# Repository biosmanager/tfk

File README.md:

# tfk - The F(ine|fancy|inal) Keyboard

This is a work in progress collection of open-source high-end keyboard PCBs. 
Designed to be hand-solderable.

**Features**:

-   Compatible with QMK firmware and VIA
-   Hot-swap sockets
-   Per-key RGB lighting and RGB backlight
-   USB-C
-   Overvoltage, overcurrent and ESD protection
-   Hand-solderable footprints
-   (All powered by STM32 microcontrollers)

> **NOTE:**  Due to the current global chip crisis I decided to use AVR based microcontrollers in the first revisions which are easier to obtain.

## Keyboards

|Status | Name  | Size | # of keys | Description | MCU | Compatible cases (intended) |
|-------| ----- | ---- | --------- | ------------|-----|------------------|
| <span style="color: green">Active</span> | tfk21-avr | 20% | 21 | Numpad with extra row   | ATmega32U4 | [KPRepublic Cospad cases](https://kprepublic.com/collections/cospad-xd24) |
| <span style="color: red">On hold</span>  | tfk21     | 20% | 21 | Numpad with extra row   | STM32F072  | [KPRepublic Cospad cases](https://kprepublic.com/collections/cospad-xd24) |
| <span style="color: red">On hold</span>  | tfk84     | 75% | 84 | More compact than a TKL | STM32F303  | [KPRepublic XD84 cases](https://kprepublic.com/collections/xd84) |

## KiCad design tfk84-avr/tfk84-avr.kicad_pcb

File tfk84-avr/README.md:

# tfk84-avr

84 key hot-swap RGB 75% TKL keyboard. Uses Microchip ATmega32U4-AU microcontroller. 
All footprints should be suitable for hand soldering.

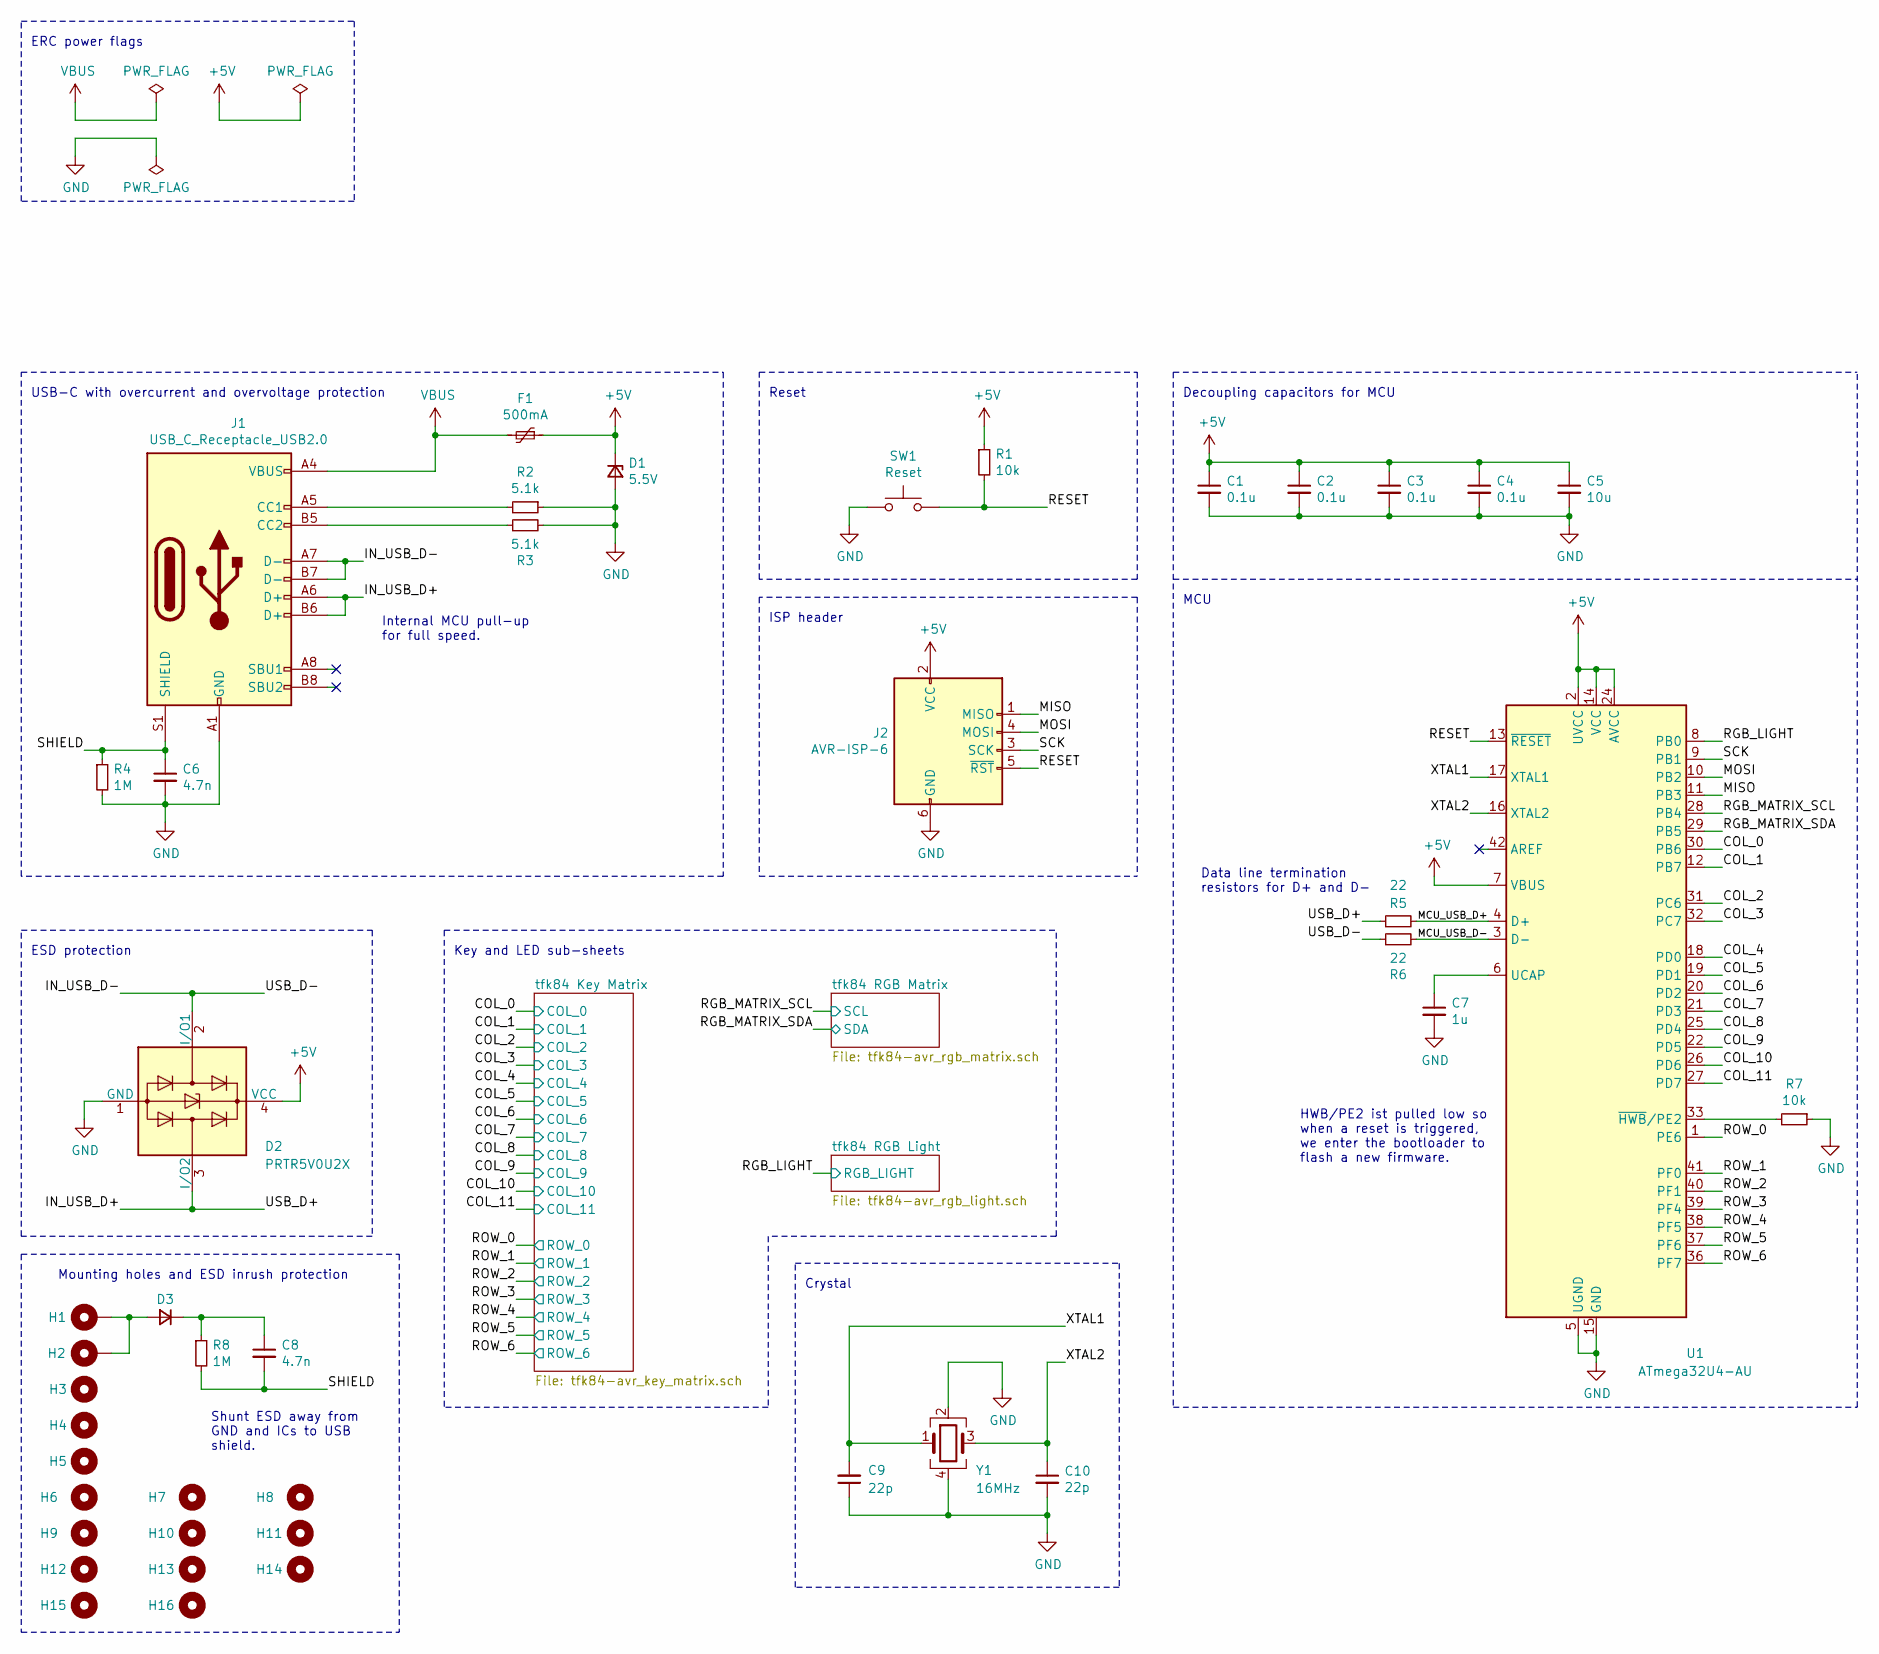
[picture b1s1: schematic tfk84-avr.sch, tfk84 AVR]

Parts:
C1, C2, C3, C4: 0.1u; C_0805_2012Metric_Pad1.18x1.45mm_HandSolder
C5: 10u; C_0805_2012Metric_Pad1.18x1.45mm_HandSolder
C6, C8: 4.7n; C_0805_2012Metric_Pad1.18x1.45mm_HandSolder
C7: 1u; C_0805_2012Metric_Pad1.18x1.45mm_HandSolder
C9, C10: 22p; C_0805_2012Metric_Pad1.18x1.45mm_HandSolder
D1: 5.5V; D_SOD-123
D2: PRTR5V0U2X; SOT-143
D3: Case ESD; D_SOD-123
F1: 500mA; Fuse_1206_3216Metric_Pad1.42x1.75mm_HandSolder
H1, H2: Case; MountingHole_2.5mm_Pad
H3, H4, H5, H6, H7, H8, H9, H10, H11, H12, H13, H14, H15, H16: MountingHole; MountingHole_4.5x2.5mm_Pad_TopOnly_NPTH
J1: USB_C_Receptacle_USB2.0; USB_C_Receptacle_HRO_TYPE-C-31-M-12
J2: AVR-ISP-6; Reset_Pretty-Mask
R1, R7: 10k; R_0805_2012Metric_Pad1.20x1.40mm_HandSolder
R2, R3: 5.1k; R_0805_2012Metric_Pad1.20x1.40mm_HandSolder
R4, R8: 1M; R_0805_2012Metric_Pad1.20x1.40mm_HandSolder
R5, R6: 22; R_0805_2012Metric_Pad1.20x1.40mm_HandSolder
SW1: Reset; SKQG-1155865
U1: ATmega32U4-AU; TQFP-44_10x10mm_P0.8mm
Y1: 16MHz; Crystal_SMD_3225-4Pin_3.2x2.5mm_HandSoldering

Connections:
+5V: C1.1, C2.1, C3.1, C4.1, C5.1, D1.1 (K), D2.4 (VCC), F1.1, J2.2 (VCC), R1.1, U1.2 (UVCC), U1.7 (VBUS), U1.14 (VCC), U1.24 (AVCC), U1.34 (VCC), U1.44 (AVCC); also elsewhere on the board
/COL_0: U1.30 (PB6); also elsewhere on the board
/COL_1: U1.12 (PB7); also elsewhere on the board
/COL_2: U1.31 (PC6); also elsewhere on the board
/COL_3: U1.32 (PC7); also elsewhere on the board
/COL_4: U1.18 (PD0); also elsewhere on the board
/COL_5: U1.19 (PD1); also elsewhere on the board
/COL_6: U1.20 (PD2); also elsewhere on the board
/COL_7: U1.21 (PD3); also elsewhere on the board
/COL_8: U1.25 (PD4); also elsewhere on the board
/COL_9: U1.22 (PD5); also elsewhere on the board
/COL_10: U1.26 (PD6); also elsewhere on the board
/COL_11: U1.27 (PD7); also elsewhere on the board
/IN_USB_D+: D2.3 (I/O2), J1.A6 (D+), J1.B6 (D+), R5.1
/IN_USB_D-: D2.2 (I/O1), J1.A7 (D-), J1.B7 (D-), R6.1
/MCU_USB_D+: R5.2, U1.4 (D+)
/MCU_USB_D-: R6.2, U1.3 (D-)
/MISO: J2.1 (MISO), U1.11 (PB3)
/MOSI: J2.4 (MOSI), U1.10 (PB2)
/RESET: J2.5 (~RST), R1.2, SW1.2, U1.13 (~RESET)
/RGB_LIGHT: U1.8 (PB0); also elsewhere on the board
/RGB_MATRIX_SCL: U1.28 (PB4); also elsewhere on the board
/RGB_MATRIX_SDA: U1.29 (PB5); also elsewhere on the board
/ROW_0: U1.1 (PE6); also elsewhere on the board
/ROW_1: U1.41 (PF0); also elsewhere on the board
/ROW_2: U1.40 (PF1); also elsewhere on the board
/ROW_3: U1.39 (PF4); also elsewhere on the board
/ROW_4: U1.38 (PF5); also elsewhere on the board
/ROW_5: U1.37 (PF6); also elsewhere on the board
/ROW_6: U1.36 (PF7); also elsewhere on the board
/SCK: J2.3 (SCK), U1.9 (PB1)
/SHIELD: C6.1, C8.2, J1.S1 (SHIELD), R4.1, R8.2
/XTAL1: C9.2, U1.17 (XTAL1), Y1.1
/XTAL2: C10.1, U1.16 (XTAL2), Y1.3
GND: C1.2, C2.2, C3.2, C4.2, C5.2, C6.2, C7.2, C9.1, C10.2, D1.2 (A), D2.1 (GND), J1.A1 (GND), J1.A12 (GND), J1.B1 (GND), J1.B12 (GND), J2.6 (GND), R2.1, R3.2, R4.2, R7.1, SW1.1, U1.5 (UGND), U1.15 (GND), U1.23 (GND), U1.35 (GND), U1.43 (GND), Y1.2, Y1.4; also elsewhere on the board
unnamed: C7.1, U1.6 (UCAP)
unnamed: C8.1, D3.1 (K), R8.1
unnamed: D3.2 (A), H1.1, H2.1
unnamed: J1.A5 (CC1), R2.2
unnamed: J1.B5 (CC2), R3.1
unnamed: R7.2, U1.33 (~HWB~/PE2)
VBUS: F1.2, J1.A4 (VBUS), J1.A9 (VBUS), J1.B4 (VBUS), J1.B9 (VBUS)

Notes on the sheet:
Internal MCU pull-up for full speed.
Decoupling capacitors for MCU
USB-C with overcurrent and overvoltage protection
Key and LED sub-sheets
ERC power flags
Mounting holes and ESD inrush protection
Shunt ESD away from GND and ICs to USB shield.
Data line termination resistors for D+ and D-
ESD protection
MCU
Crystal
HWB/PE2 ist pulled low so when a reset is triggered, we enter the bootloader to flash a new firmware.
Reset
ISP header

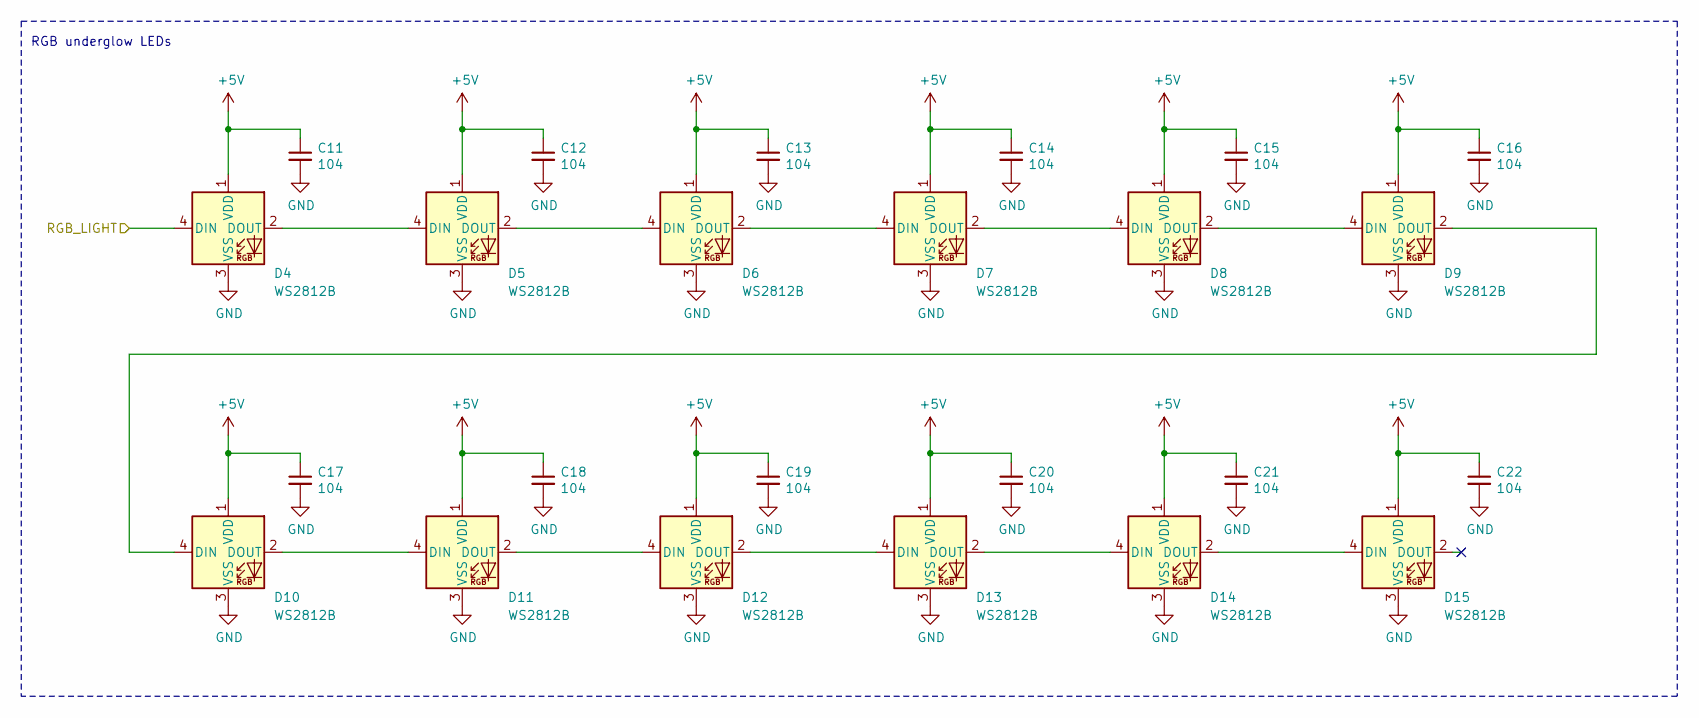
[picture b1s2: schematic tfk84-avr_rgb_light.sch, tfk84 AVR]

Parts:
C11, C12, C13, C14, C15, C16, C17, C18, C19, C20, C21, C22: 104; C_0805_2012Metric_Pad1.18x1.45mm_HandSolder
D4, D5, D6, D7, D8, D9, D10, D11, D12, D13, D14, D15: WS2812B; LED_WS2812B_PLCC4_5.0x5.0mm_P3.2mm

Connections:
+5V: C11.1, C12.1, C13.1, C14.1, C15.1, C16.1, C17.1, C18.1, C19.1, C20.1, C21.1, C22.1, D4.1 (VDD), D5.1 (VDD), D6.1 (VDD), D7.1 (VDD), D8.1 (VDD), D9.1 (VDD), D10.1 (VDD), D11.1 (VDD), D12.1 (VDD), D13.1 (VDD), D14.1 (VDD), D15.1 (VDD); also elsewhere on the board
/RGB_LIGHT: D4.4 (DIN); also elsewhere on the board
GND: C11.2, C12.2, C13.2, C14.2, C15.2, C16.2, C17.2, C18.2, C19.2, C20.2, C21.2, C22.2, D4.3 (VSS), D5.3 (VSS), D6.3 (VSS), D7.3 (VSS), D8.3 (VSS), D9.3 (VSS), D10.3 (VSS), D11.3 (VSS), D12.3 (VSS), D13.3 (VSS), D14.3 (VSS), D15.3 (VSS); also elsewhere on the board
unnamed: D4.2 (DOUT), D5.4 (DIN)
unnamed: D5.2 (DOUT), D6.4 (DIN)
unnamed: D6.2 (DOUT), D7.4 (DIN)
unnamed: D7.2 (DOUT), D8.4 (DIN)
unnamed: D8.2 (DOUT), D9.4 (DIN)
unnamed: D10.2 (DOUT), D11.4 (DIN)
unnamed: D9.2 (DOUT), D10.4 (DIN)
unnamed: D11.2 (DOUT), D12.4 (DIN)
unnamed: D12.2 (DOUT), D13.4 (DIN)
unnamed: D13.2 (DOUT), D14.4 (DIN)
unnamed: D14.2 (DOUT), D15.4 (DIN)

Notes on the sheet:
RGB underglow LEDs

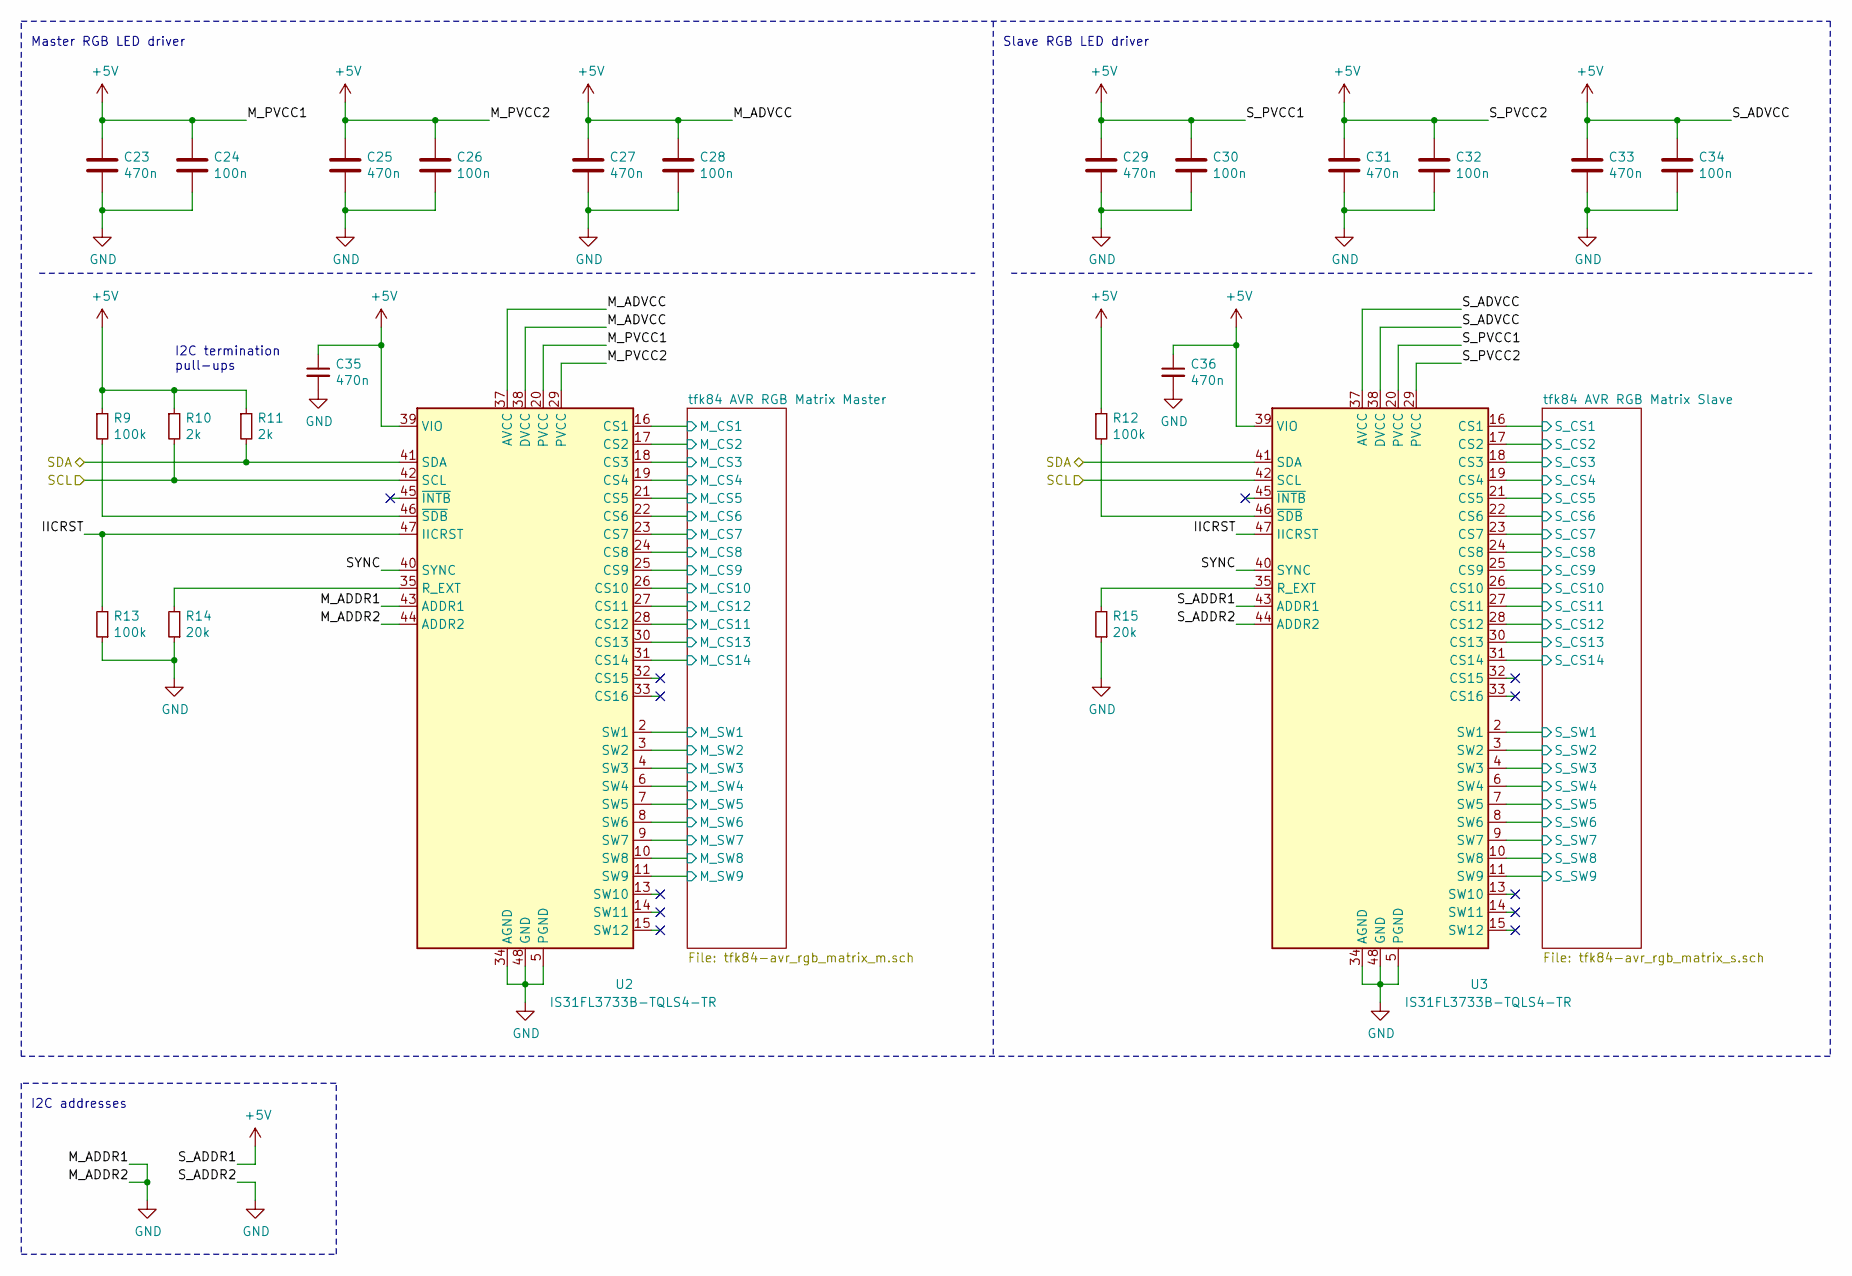
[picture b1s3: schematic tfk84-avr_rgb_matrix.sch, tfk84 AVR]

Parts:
C23, C25, C27, C29, C31, C33, C35, C36: 470n; C_0805_2012Metric_Pad1.18x1.45mm_HandSolder
C24, C26, C28, C30, C32, C34: 100n; C_0805_2012Metric_Pad1.18x1.45mm_HandSolder
R9, R12, R13: 100k; R_0805_2012Metric_Pad1.20x1.40mm_HandSolder
R10, R11: 2k; R_0805_2012Metric_Pad1.20x1.40mm_HandSolder
R14, R15: 20k; R_0805_2012Metric_Pad1.20x1.40mm_HandSolder
U2, U3: IS31FL3733B-TQLS4-TR; TQFP-48-1EP_7x7mm_P0.5mm_EP5x5mm_ThermalVias

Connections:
+5V: C23.1, C24.1, C25.1, C26.1, C27.1, C28.2, C29.1, C30.1, C31.1, C32.1, C33.1, C34.2, C35.1, C36.1, R9.1, R10.1, R11.1, R12.1, U2.20 (PVCC), U2.29 (PVCC), U2.37 (AVCC), U2.38 (DVCC), U2.39 (VIO), U3.20 (PVCC), U3.29 (PVCC), U3.37 (AVCC), U3.38 (DVCC), U3.39 (VIO), U3.43 (ADDR1); also elsewhere on the board
/RGB_MATRIX_SCL: R10.2, U2.42 (SCL), U3.42 (SCL); also elsewhere on the board
/RGB_MATRIX_SDA: R11.2, U2.41 (SDA), U3.41 (SDA); also elsewhere on the board
/tfk84 RGB Matrix/IICRST: R13.2, U2.47 (IICRST), U3.47 (IICRST)
/tfk84 RGB Matrix/SYNC: U2.40 (SYNC), U3.40 (SYNC)
/tfk84 RGB Matrix/tfk84 AVR RGB Matrix Master/M_CS1: U2.16 (CS1); also elsewhere on the board
/tfk84 RGB Matrix/tfk84 AVR RGB Matrix Master/M_CS2: U2.17 (CS2); also elsewhere on the board
/tfk84 RGB Matrix/tfk84 AVR RGB Matrix Master/M_CS3: U2.18 (CS3); also elsewhere on the board
/tfk84 RGB Matrix/tfk84 AVR RGB Matrix Master/M_CS4: U2.19 (CS4); also elsewhere on the board
/tfk84 RGB Matrix/tfk84 AVR RGB Matrix Master/M_CS5: U2.21 (CS5); also elsewhere on the board
/tfk84 RGB Matrix/tfk84 AVR RGB Matrix Master/M_CS6: U2.22 (CS6); also elsewhere on the board
/tfk84 RGB Matrix/tfk84 AVR RGB Matrix Master/M_CS7: U2.23 (CS7); also elsewhere on the board
/tfk84 RGB Matrix/tfk84 AVR RGB Matrix Master/M_CS8: U2.24 (CS8); also elsewhere on the board
/tfk84 RGB Matrix/tfk84 AVR RGB Matrix Master/M_CS9: U2.25 (CS9); also elsewhere on the board
/tfk84 RGB Matrix/tfk84 AVR RGB Matrix Master/M_CS10: U2.26 (CS10); also elsewhere on the board
/tfk84 RGB Matrix/tfk84 AVR RGB Matrix Master/M_CS11: U2.28 (CS12); also elsewhere on the board
/tfk84 RGB Matrix/tfk84 AVR RGB Matrix Master/M_CS12: U2.27 (CS11); also elsewhere on the board
/tfk84 RGB Matrix/tfk84 AVR RGB Matrix Master/M_CS13: U2.30 (CS13); also elsewhere on the board
/tfk84 RGB Matrix/tfk84 AVR RGB Matrix Master/M_CS14: U2.31 (CS14); also elsewhere on the board
/tfk84 RGB Matrix/tfk84 AVR RGB Matrix Master/M_SW1: U2.2 (SW1); also elsewhere on the board
/tfk84 RGB Matrix/tfk84 AVR RGB Matrix Master/M_SW2: U2.3 (SW2); also elsewhere on the board
/tfk84 RGB Matrix/tfk84 AVR RGB Matrix Master/M_SW3: U2.4 (SW3); also elsewhere on the board
/tfk84 RGB Matrix/tfk84 AVR RGB Matrix Master/M_SW4: U2.6 (SW4); also elsewhere on the board
/tfk84 RGB Matrix/tfk84 AVR RGB Matrix Master/M_SW5: U2.7 (SW5); also elsewhere on the board
/tfk84 RGB Matrix/tfk84 AVR RGB Matrix Master/M_SW6: U2.8 (SW6); also elsewhere on the board
/tfk84 RGB Matrix/tfk84 AVR RGB Matrix Master/M_SW7: U2.9 (SW7); also elsewhere on the board
/tfk84 RGB Matrix/tfk84 AVR RGB Matrix Master/M_SW8: U2.10 (SW8); also elsewhere on the board
/tfk84 RGB Matrix/tfk84 AVR RGB Matrix Master/M_SW9: U2.11 (SW9); also elsewhere on the board
/tfk84 RGB Matrix/tfk84 AVR RGB Matrix Slave/S_CS1: U3.16 (CS1); also elsewhere on the board
/tfk84 RGB Matrix/tfk84 AVR RGB Matrix Slave/S_CS2: U3.17 (CS2); also elsewhere on the board
/tfk84 RGB Matrix/tfk84 AVR RGB Matrix Slave/S_CS3: U3.18 (CS3); also elsewhere on the board
/tfk84 RGB Matrix/tfk84 AVR RGB Matrix Slave/S_CS4: U3.19 (CS4); also elsewhere on the board
/tfk84 RGB Matrix/tfk84 AVR RGB Matrix Slave/S_CS5: U3.21 (CS5); also elsewhere on the board
/tfk84 RGB Matrix/tfk84 AVR RGB Matrix Slave/S_CS6: U3.22 (CS6); also elsewhere on the board
/tfk84 RGB Matrix/tfk84 AVR RGB Matrix Slave/S_CS7: U3.23 (CS7); also elsewhere on the board
/tfk84 RGB Matrix/tfk84 AVR RGB Matrix Slave/S_CS8: U3.24 (CS8); also elsewhere on the board
/tfk84 RGB Matrix/tfk84 AVR RGB Matrix Slave/S_CS9: U3.25 (CS9); also elsewhere on the board
/tfk84 RGB Matrix/tfk84 AVR RGB Matrix Slave/S_CS10: U3.26 (CS10); also elsewhere on the board
/tfk84 RGB Matrix/tfk84 AVR RGB Matrix Slave/S_CS11: U3.27 (CS11); also elsewhere on the board
/tfk84 RGB Matrix/tfk84 AVR RGB Matrix Slave/S_CS12: U3.28 (CS12); also elsewhere on the board
/tfk84 RGB Matrix/tfk84 AVR RGB Matrix Slave/S_CS13: U3.30 (CS13); also elsewhere on the board
/tfk84 RGB Matrix/tfk84 AVR RGB Matrix Slave/S_CS14: U3.31 (CS14); also elsewhere on the board
/tfk84 RGB Matrix/tfk84 AVR RGB Matrix Slave/S_SW1: U3.2 (SW1); also elsewhere on the board
/tfk84 RGB Matrix/tfk84 AVR RGB Matrix Slave/S_SW2: U3.3 (SW2); also elsewhere on the board
/tfk84 RGB Matrix/tfk84 AVR RGB Matrix Slave/S_SW3: U3.4 (SW3); also elsewhere on the board
/tfk84 RGB Matrix/tfk84 AVR RGB Matrix Slave/S_SW4: U3.6 (SW4); also elsewhere on the board
/tfk84 RGB Matrix/tfk84 AVR RGB Matrix Slave/S_SW5: U3.7 (SW5); also elsewhere on the board
/tfk84 RGB Matrix/tfk84 AVR RGB Matrix Slave/S_SW6: U3.8 (SW6); also elsewhere on the board
/tfk84 RGB Matrix/tfk84 AVR RGB Matrix Slave/S_SW7: U3.9 (SW7); also elsewhere on the board
/tfk84 RGB Matrix/tfk84 AVR RGB Matrix Slave/S_SW8: U3.10 (SW8); also elsewhere on the board
/tfk84 RGB Matrix/tfk84 AVR RGB Matrix Slave/S_SW9: U3.11 (SW9); also elsewhere on the board
GND: C23.2, C24.2, C25.2, C26.2, C27.2, C28.1, C29.2, C30.2, C31.2, C32.2, C33.2, C34.1, C35.2, C36.2, R13.1, R14.1, R15.1, U2.5 (PGND), U2.12 (PGND), U2.34 (AGND), U2.43 (ADDR1), U2.44 (ADDR2), U2.48 (GND), U2.49 (GND), U3.5 (PGND), U3.12 (PGND), U3.34 (AGND), U3.44 (ADDR2), U3.48 (GND), U3.49 (GND); also elsewhere on the board
unnamed: R9.2, U2.46 (~SDB)
unnamed: R12.2, U3.46 (~SDB)
unnamed: R14.2, U2.35 (R_EXT)
unnamed: R15.2, U3.35 (R_EXT)

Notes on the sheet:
I2C termination pull-ups
I2C addresses
Master RGB LED driver
Slave RGB LED driver

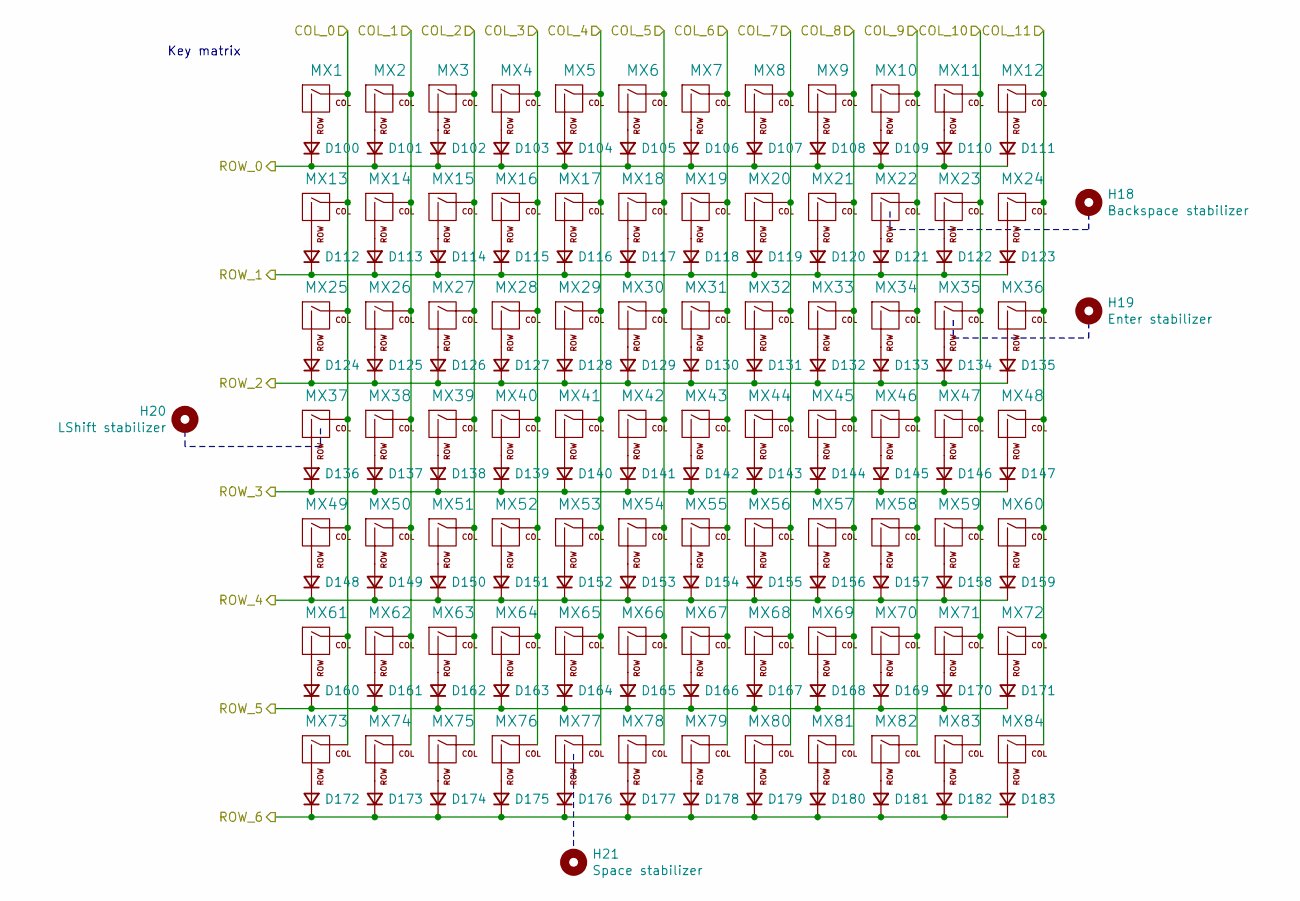
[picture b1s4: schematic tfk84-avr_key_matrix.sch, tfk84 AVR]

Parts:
D100, D101, D102, D103, D104, D105, D106, D107, D108, D109, D110, D111, D112, D113, D114, D115, D116, D117, D118, D119, D120, D121, D122, D123, D124, D125, D126, D127, D128, D129, D130, D131, D132, D133, D134, D135, D136, D137, D138, D139, D140, D141, D142, D143, D144, D145, D146, D147, D148, D149, D150, D151, D152, D153, D154, D155, D156, D157, D158, D159, D160, D161, D162, D163, D164, D165, D166, D167, D168, D169, D170, D171, D172, D173, D174, D175, D176, D177, D178, D179, D180, D181, D182, D183: D_Small; D_SOD-123
H18: Backspace stabilizer; Stabilizer_Cherry_MX_2u_CrtYd
H19: Enter stabilizer; Stabilizer_Cherry_MX_2u_CrtYd
H20: LShift stabilizer; Stabilizer_Cherry_MX_2u_CrtYd
H21: Space stabilizer; Stabilizer_Cherry_MX_6.25u
MX1, MX2, MX3, MX4, MX5, MX6, MX7, MX8, MX9, MX11, MX12, MX15, MX16, MX18, MX20, MX21, MX24, MX26, MX27, MX28, MX29, MX30, MX31, MX32, MX33, MX34, MX36, MX39, MX40, MX41, MX42, MX43, MX44, MX45, MX46, MX47, MX48, MX50, MX51, MX52, MX54, MX56, MX57, MX58, MX60, MX63, MX64, MX65, MX66, MX67, MX68, MX69, MX70, MX72, MX74, MX75, MX76, MX78, MX79, MX80, MX81, MX82, MX83, MX84: MX-NoLED; SW_Hotswap_Kailh_1.00u_NoFrontSilk
MX10, MX14, MX17, MX19, MX38, MX53, MX55, MX62, MX71: MX-NoLED; SW_Hotswap_Kailh_1.00u_NoFrontSilk_CornerPad
MX13: MX-NoLED; SW_Hotswap_Kailh_1.50u_NoFrontSilk_CornerPad
MX22: MX-NoLED; SW_Hotswap_Kailh_2.00u_NoFrontSilk
MX23: MX-NoLED; SW_Hotswap_Kailh_1.50u_NoFrontSilk
MX25, MX59: MX-NoLED; SW_Hotswap_Kailh_1.75u_NoFrontSilk
MX35, MX37: MX-NoLED; SW_Hotswap_Kailh_2.25u_NoFrontSilk
MX49, MX61, MX73: MX-NoLED; SW_Hotswap_Kailh_1.25u_NoFrontSilk
MX77: MX-NoLED; SW_Hotswap_Kailh_6.25u_NoFrontSilk

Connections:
/COL_0: MX1.1 (COL), MX13.1 (COL), MX25.1 (COL), MX37.1 (COL), MX49.1 (COL), MX61.1 (COL), MX73.1 (COL); also elsewhere on the board
/COL_1: MX2.1 (COL), MX14.1 (COL), MX26.1 (COL), MX38.1 (COL), MX50.1 (COL), MX62.1 (COL), MX74.1 (COL); also elsewhere on the board
/COL_2: MX3.1 (COL), MX15.1 (COL), MX27.1 (COL), MX39.1 (COL), MX51.1 (COL), MX63.1 (COL), MX75.1 (COL); also elsewhere on the board
/COL_3: MX4.1 (COL), MX16.1 (COL), MX28.1 (COL), MX40.1 (COL), MX52.1 (COL), MX64.1 (COL), MX76.1 (COL); also elsewhere on the board
/COL_4: MX5.1 (COL), MX17.1 (COL), MX29.1 (COL), MX41.1 (COL), MX53.1 (COL), MX65.1 (COL), MX77.1 (COL); also elsewhere on the board
/COL_5: MX6.1 (COL), MX18.1 (COL), MX30.1 (COL), MX42.1 (COL), MX54.1 (COL), MX66.1 (COL), MX78.1 (COL); also elsewhere on the board
/COL_6: MX7.1 (COL), MX19.1 (COL), MX31.1 (COL), MX43.1 (COL), MX55.1 (COL), MX67.1 (COL), MX79.1 (COL); also elsewhere on the board
/COL_7: MX8.1 (COL), MX20.1 (COL), MX32.1 (COL), MX44.1 (COL), MX56.1 (COL), MX68.1 (COL), MX80.1 (COL); also elsewhere on the board
/COL_8: MX9.1 (COL), MX21.1 (COL), MX33.1 (COL), MX45.1 (COL), MX57.1 (COL), MX69.1 (COL), MX81.1 (COL); also elsewhere on the board
/COL_9: MX10.1 (COL), MX22.1 (COL), MX34.1 (COL), MX46.1 (COL), MX58.1 (COL), MX70.1 (COL), MX82.1 (COL); also elsewhere on the board
/COL_10: MX11.1 (COL), MX23.1 (COL), MX35.1 (COL), MX47.1 (COL), MX59.1 (COL), MX71.1 (COL), MX83.1 (COL); also elsewhere on the board
/COL_11: MX12.1 (COL), MX24.1 (COL), MX36.1 (COL), MX48.1 (COL), MX60.1 (COL), MX72.1 (COL), MX84.1 (COL); also elsewhere on the board
/ROW_0: D100.1 (K), D101.1 (K), D102.1 (K), D103.1 (K), D104.1 (K), D105.1 (K), D106.1 (K), D107.1 (K), D108.1 (K), D109.1 (K), D110.1 (K), D111.1 (K); also elsewhere on the board
/ROW_1: D112.1 (K), D113.1 (K), D114.1 (K), D115.1 (K), D116.1 (K), D117.1 (K), D118.1 (K), D119.1 (K), D120.1 (K), D121.1 (K), D122.1 (K), D123.1 (K); also elsewhere on the board
/ROW_2: D124.1 (K), D125.1 (K), D126.1 (K), D127.1 (K), D128.1 (K), D129.1 (K), D130.1 (K), D131.1 (K), D132.1 (K), D133.1 (K), D134.1 (K), D135.1 (K); also elsewhere on the board
/ROW_3: D136.1 (K), D137.1 (K), D138.1 (K), D139.1 (K), D140.1 (K), D141.1 (K), D142.1 (K), D143.1 (K), D144.1 (K), D145.1 (K), D146.1 (K), D147.1 (K); also elsewhere on the board
/ROW_4: D148.1 (K), D149.1 (K), D150.1 (K), D151.1 (K), D152.1 (K), D153.1 (K), D154.1 (K), D155.1 (K), D156.1 (K), D157.1 (K), D158.1 (K), D159.1 (K); also elsewhere on the board
/ROW_5: D160.1 (K), D161.1 (K), D162.1 (K), D163.1 (K), D164.1 (K), D165.1 (K), D166.1 (K), D167.1 (K), D168.1 (K), D169.1 (K), D170.1 (K), D171.1 (K); also elsewhere on the board
/ROW_6: D172.1 (K), D173.1 (K), D174.1 (K), D175.1 (K), D176.1 (K), D177.1 (K), D178.1 (K), D179.1 (K), D180.1 (K), D181.1 (K), D182.1 (K), D183.1 (K); also elsewhere on the board
unnamed: D100.2 (A), MX1.2 (ROW)
unnamed: D101.2 (A), MX2.2 (ROW)
unnamed: D102.2 (A), MX3.2 (ROW)
unnamed: D103.2 (A), MX4.2 (ROW)
unnamed: D104.2 (A), MX5.2 (ROW)
unnamed: D105.2 (A), MX6.2 (ROW)
unnamed: D106.2 (A), MX7.2 (ROW)
unnamed: D107.2 (A), MX8.2 (ROW)
unnamed: D108.2 (A), MX9.2 (ROW)
unnamed: D109.2 (A), MX10.2 (ROW)
unnamed: D110.2 (A), MX11.2 (ROW)
unnamed: D111.2 (A), MX12.2 (ROW)
unnamed: D112.2 (A), MX13.2 (ROW)
unnamed: D113.2 (A), MX14.2 (ROW)
unnamed: D114.2 (A), MX15.2 (ROW)
unnamed: D115.2 (A), MX16.2 (ROW)
unnamed: D116.2 (A), MX17.2 (ROW)
unnamed: D117.2 (A), MX18.2 (ROW)
unnamed: D118.2 (A), MX19.2 (ROW)
unnamed: D119.2 (A), MX20.2 (ROW)
unnamed: D120.2 (A), MX21.2 (ROW)
unnamed: D121.2 (A), MX22.2 (ROW)
unnamed: D122.2 (A), MX23.2 (ROW)
unnamed: D123.2 (A), MX24.2 (ROW)
unnamed: D124.2 (A), MX25.2 (ROW)
unnamed: D125.2 (A), MX26.2 (ROW)
unnamed: D126.2 (A), MX27.2 (ROW)
unnamed: D127.2 (A), MX28.2 (ROW)
unnamed: D128.2 (A), MX29.2 (ROW)
unnamed: D129.2 (A), MX30.2 (ROW)
unnamed: D130.2 (A), MX31.2 (ROW)
unnamed: D131.2 (A), MX32.2 (ROW)
unnamed: D132.2 (A), MX33.2 (ROW)
unnamed: D133.2 (A), MX34.2 (ROW)
unnamed: D134.2 (A), MX35.2 (ROW)
unnamed: D135.2 (A), MX36.2 (ROW)
unnamed: D136.2 (A), MX37.2 (ROW)
unnamed: D137.2 (A), MX38.2 (ROW)
unnamed: D138.2 (A), MX39.2 (ROW)
unnamed: D139.2 (A), MX40.2 (ROW)
unnamed: D140.2 (A), MX41.2 (ROW)
unnamed: D141.2 (A), MX42.2 (ROW)
unnamed: D142.2 (A), MX43.2 (ROW)
unnamed: D143.2 (A), MX44.2 (ROW)
unnamed: D144.2 (A), MX45.2 (ROW)
unnamed: D145.2 (A), MX46.2 (ROW)
unnamed: D146.2 (A), MX47.2 (ROW)
unnamed: D147.2 (A), MX48.2 (ROW)
unnamed: D148.2 (A), MX49.2 (ROW)
unnamed: D149.2 (A), MX50.2 (ROW)
unnamed: D150.2 (A), MX51.2 (ROW)
unnamed: D151.2 (A), MX52.2 (ROW)
unnamed: D152.2 (A), MX53.2 (ROW)
unnamed: D153.2 (A), MX54.2 (ROW)
unnamed: D154.2 (A), MX55.2 (ROW)
unnamed: D155.2 (A), MX56.2 (ROW)
unnamed: D156.2 (A), MX57.2 (ROW)
unnamed: D157.2 (A), MX58.2 (ROW)
unnamed: D158.2 (A), MX59.2 (ROW)
unnamed: D159.2 (A), MX60.2 (ROW)
unnamed: D160.2 (A), MX61.2 (ROW)
unnamed: D161.2 (A), MX62.2 (ROW)
unnamed: D162.2 (A), MX63.2 (ROW)
unnamed: D163.2 (A), MX64.2 (ROW)
unnamed: D164.2 (A), MX65.2 (ROW)
unnamed: D165.2 (A), MX66.2 (ROW)
unnamed: D166.2 (A), MX67.2 (ROW)
unnamed: D167.2 (A), MX68.2 (ROW)
unnamed: D168.2 (A), MX69.2 (ROW)
unnamed: D169.2 (A), MX70.2 (ROW)
unnamed: D170.2 (A), MX71.2 (ROW)
unnamed: D171.2 (A), MX72.2 (ROW)
unnamed: D172.2 (A), MX73.2 (ROW)
unnamed: D173.2 (A), MX74.2 (ROW)
unnamed: D174.2 (A), MX75.2 (ROW)
unnamed: D175.2 (A), MX76.2 (ROW)
unnamed: D176.2 (A), MX77.2 (ROW)
unnamed: D177.2 (A), MX78.2 (ROW)
unnamed: D178.2 (A), MX79.2 (ROW)
unnamed: D179.2 (A), MX80.2 (ROW)
unnamed: D180.2 (A), MX81.2 (ROW)
unnamed: D181.2 (A), MX82.2 (ROW)
unnamed: D182.2 (A), MX83.2 (ROW)
unnamed: D183.2 (A), MX84.2 (ROW)

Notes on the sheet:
Key matrix
